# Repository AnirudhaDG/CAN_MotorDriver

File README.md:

# CAN_MotorDriver
## Overview

This motor driver is designed for high-power applications, supporting motors up to 30V at 30A. It integrates CAN and UART communication, enabling advanced control modes and seamless daisy chaining. Powered by an STM32 microcontroller, it features onboard smoothing algorithms for precise motor control. The driver also includes protection circuitry to ensure safe and reliable operation.
## Features

    1. High Power Output: Supports motors up to 30V and 30A.
    2. CAN and UART Communication: Enables flexible control, networking, and daisy chaining of multiple drivers.
    3. TC4427 Gate Driver: Ensures efficient and reliable MOSFET switching.
    4. STM32 Microcontroller: Provides advanced control modes, real-time processing, and communication support.
    5. USB Type-C Power Input: Allows flexible power options and supports USB Full Speed (USBFS) for data communication.
    6. Protection Circuitry: Includes overcurrent, thermal, and voltage protection for safe operation.
    7. Smoothing Algorithms: Reduces noise and enhances motor response for smoother motion.

## Communication Interfaces

    1. CAN Bus: Enables robust multi-node communication and supports real-time control in industrial and robotic applications.
    2. UART: Provides simple serial communication for direct control or debugging.
    3. USB Full Speed (USBFS): Allows firmware updates and direct communication with a host device.

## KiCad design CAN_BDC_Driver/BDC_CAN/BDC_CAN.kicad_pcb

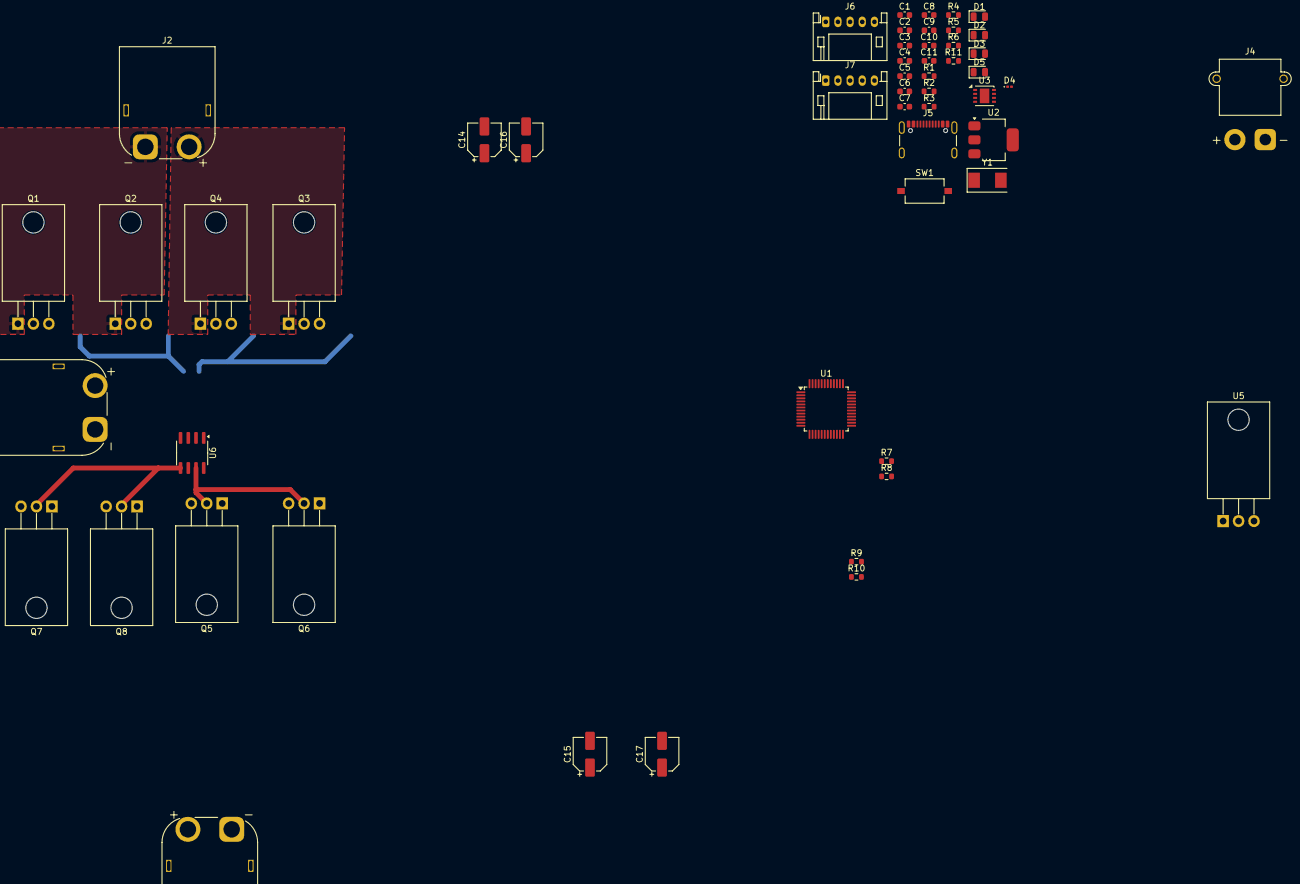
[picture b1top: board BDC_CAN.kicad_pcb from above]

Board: 2 copper layers, 54 parts (1 on the bottom side), 38 nets.

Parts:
C1, C2: 20p; C_0603_1608Metric
C3, C5, C6, C7, C8: 100n; C_0603_1608Metric
C4: 10n; C_0603_1608Metric
C9, C10: 4.7u; C_0603_1608Metric
C11: 100p; C_0603_1608Metric
C14, C15, C16, C17: 2200uF; CP_Elec_5x5.4
D1, D2, D3, D5: Stat_LED; LED_0805_2012Metric
D4: D; D_0201_0603Metric
J1: VCC_IN; AMASS_XT60PW-M_1x02_P7.20mm_Horizontal
J2: Motor1_Out; AMASS_XT60PW-M_1x02_P7.20mm_Horizontal
J3: Motor2_Out; AMASS_XT60PW-M_1x02_P7.20mm_Horizontal
J4: CAN; AMASS_XT30PW-M_1x02_P2.50mm_Horizontal
J5: USB_C_Receptacle_USB2.0_16P; USB_C_Receptacle_GCT_USB4105-xx-A_16P_TopMnt_Horizontal
J6, J7: Conn_01x05_Pin; JST_PH_S5B-PH-K_1x05_P2.00mm_Horizontal
Q1, Q3, Q5, Q7: PMOS; TO-220-3_Horizontal_TabDown
Q2, Q4, Q6, Q8: NMOS; TO-220-3_Horizontal_TabDown
R1, R2, R3, R6, R11: 120; R_0603_1608Metric
R4: 1k5; R_0603_1608Metric
R5: 1.1M; R_0603_1608Metric
R7, R8, R9, R10: 10k; R_0603_1608Metric
SW1: SW_Push; SW_Tactile_SPST_NO_Straight_CK_PTS636Sx25SMTRLFS
U1: STM32F103C8T6; LQFP-48_7x7mm_P0.5mm
U2: AMS1117; SOT-223-3_TabPin2
U3: MCP2561-E-MF; DFN-8-1EP_3x3mm_P0.65mm_EP1.55x2.4mm
U4, U6: TC4427xOA; SOIC-8_3.9x4.9mm_P1.27mm
U5: L7805; TO-220-3_Horizontal_TabDown
Y1: Crystal; Crystal_SMD_0603-2Pin_6.0x3.5mm

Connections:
+3.3V: C3.1, C5.1, C6.1, C7.1, C8.1, C10.2, J6.2, J7.2, U1.1 (VBAT), U1.9 (VDDA), U1.24 (VDD), U1.36 (VDD), U1.48 (VDD), U3.3 (VDD)
/Driver+FETS1/A: Q5.2 (G), Q6.2 (G), R9.2, U6.7 (OUT_A)
/Driver+FETS1/B: Q7.2 (G), Q8.2 (G), R10.1, U6.5 (OUT_B)
/Driver+FETS1/MA: C15.1, J3.1, Q5.1 (D), Q6.1 (D)
/Driver+FETS1/MB: C17.1, J3.2, Q7.1 (D), Q8.1 (D)
/Driver+FETS1/PWM1: R3.1, U1.17 (PA7), U6.2 (IN_A), U6.4 (IN_B)
/Driver+FETS/5V: C9.1, D4.1 (K), J6.5, J7.5, U4.6 (VDD), U5.3 (OUT), U6.6 (VDD)
/Driver+FETS/A: Q1.2 (G), Q2.2 (G), R7.2, U4.7 (OUT_A)
/Driver+FETS/B: Q3.2 (G), Q4.2 (G), R8.1, U4.5 (OUT_B)
/Driver+FETS/MA: C14.1, J2.1, Q1.1 (D), Q2.1 (D)
/Driver+FETS/MB: C16.1, J2.2, Q3.1 (D), Q4.1 (D)
/Driver+FETS/PWM1: R1.1, U1.41 (PB5), U4.2 (IN_A), U4.4 (IN_B)
/Driver+FETS/VCC: J1.2, Q1.3 (S), Q3.3 (S), Q5.3 (S), Q7.3 (S), U5.1 (IN)
/mC/CAN_H: C11.1, J4.2, R6.1, U3.7 (CANH)
/mC/CAN_L: C11.2, J4.1, R6.2, U3.6 (CANL)
/mC/CAN_RX: U1.45 (PB8), U3.4 (RXD)
/mC/CAN_TX: U1.46 (PB9), U3.1 (TXD)
/mC/HSE_IN: C2.2, U1.6 (PD1), Y1.2
/mC/HSE_OUT: C1.2, U1.5 (PD0), Y1.1
/mC/SCL: J7.3, U1.40 (PB4)
/mC/SDA: J7.4, U1.39 (PB3)
/mC/Stat1: R2.1, U1.26 (PB13)
/mC/Stat2: R11.1, U1.25 (PB12)
/mC/UART_RX: J6.4, U1.22 (PB11)
/mC/UART_TX: J6.3, U1.21 (PB10)
GND: C1.1, C2.1, C3.2, C5.2, C6.2, C7.2, C8.2, C14.2, C15.2, C16.2, C17.2, D1.1 (K), D2.1 (K), D3.1 (K), D5.1 (K), J1.1, J5.A1 (GND), J5.A12 (GND), J5.B1 (GND), J5.B12 (GND), J5.S1 (SHIELD), J6.1, J7.1, Q2.3 (S), Q4.3 (S), Q6.3 (S), Q8.3 (S), R5.1, R7.1, R8.2, R9.1, R10.2, SW1.1, U1.8 (VSSA), U1.23 (VSS), U1.35 (VSS), U1.44 (BOOT0), U1.47 (VSS), U2.1 (ADJ), U3.2 (VSS), U3.9 (VSS), U4.3 (GND), U5.2 (GND), U6.3 (GND)
unnamed: C4.2, SW1.2
unnamed: D1.2 (A), R1.2
unnamed: D2.2 (A), R2.2
unnamed: D3.2 (A), R3.2
unnamed: D4.2 (A), J5.A4 (VBUS), J5.A9 (VBUS), J5.B4 (VBUS), J5.B9 (VBUS)
unnamed: D5.2 (A), R11.2
unnamed: C4.1, U1.7 (NRST)
unnamed: C9.2, U2.3 (VI)
unnamed: C10.1, U2.2 (VO)
unnamed: R5.2, U3.8 (STBY)
USB_D+: J5.B6 (D+), R4.2, U1.33 (PA12)
USB_D-: J5.B7 (D-), U1.32 (PA11)

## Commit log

2025-03-04 V0.1
2025-03-05 README updated
2025-04-18 Placement Changed
2025-04-18 New Design
